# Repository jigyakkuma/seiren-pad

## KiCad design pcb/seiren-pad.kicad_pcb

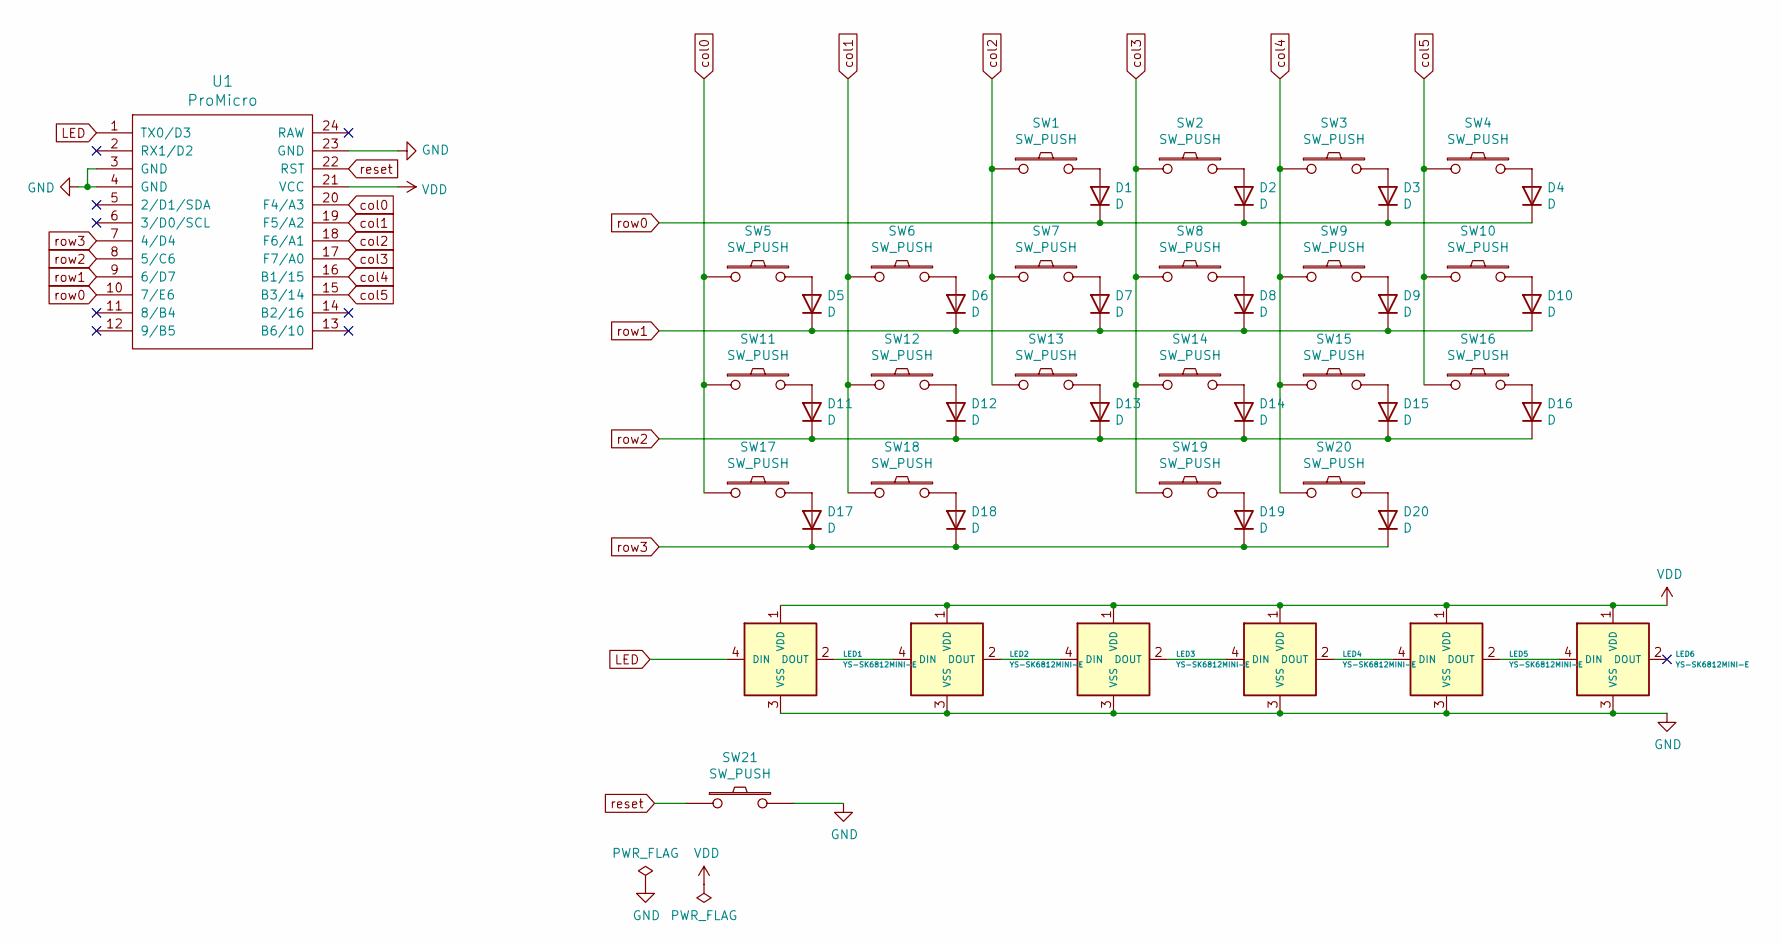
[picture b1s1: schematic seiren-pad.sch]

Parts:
D1, D2, D3, D4, D5, D6, D7, D8, D9, D10, D11, D12, D13, D14, D15, D16, D17, D18, D19, D20: D; D3_SMD_v2
LED1, LED2, LED3, LED4, LED5, LED6: YS-SK6812MINI-E
SW1, SW2, SW3, SW4, SW5, SW6, SW7, SW8, SW9, SW10, SW11, SW12, SW13, SW14, SW15, SW16, SW17, SW18, SW19, SW20: SW_PUSH; CherryMX_Hotswap
SW21: SW_PUSH; SW_Tactile_SPST_Angled_MJTP1117
U1: ProMicro; ProMicro_v3

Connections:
GND: LED1.3 (VSS), LED2.3 (VSS), LED3.3 (VSS), LED4.3 (VSS), LED5.3 (VSS), LED6.3 (VSS), SW21.2, U1.3 (GND), U1.4 (GND), U1.23 (GND)
LED: LED1.4 (DIN), U1.1 (TX0/D3)
unnamed: D1.2 (A), SW1.2
unnamed: D2.2 (A), SW2.2
unnamed: D3.2 (A), SW3.2
unnamed: D4.2 (A), SW4.2
unnamed: D5.2 (A), SW5.2
unnamed: D6.2 (A), SW6.2
unnamed: D7.2 (A), SW7.2
unnamed: D8.2 (A), SW8.2
unnamed: D9.2 (A), SW9.2
unnamed: D10.2 (A), SW10.2
unnamed: D11.2 (A), SW11.2
unnamed: D12.2 (A), SW12.2
unnamed: D13.2 (A), SW13.2
unnamed: D14.2 (A), SW14.2
unnamed: D15.2 (A), SW15.2
unnamed: D16.2 (A), SW16.2
unnamed: D17.2 (A), SW17.2
unnamed: D18.2 (A), SW18.2
unnamed: D19.2 (A), SW19.2
unnamed: D20.2 (A), SW20.2
unnamed: LED1.2 (DOUT), LED2.4 (DIN)
unnamed: LED2.2 (DOUT), LED3.4 (DIN)
unnamed: LED3.2 (DOUT), LED4.4 (DIN)
unnamed: LED4.2 (DOUT), LED5.4 (DIN)
unnamed: LED5.2 (DOUT), LED6.4 (DIN)
VDD: LED1.1 (VDD), LED2.1 (VDD), LED3.1 (VDD), LED4.1 (VDD), LED5.1 (VDD), LED6.1 (VDD), U1.21 (VCC)
col0: SW5.1, SW11.1, SW17.1, U1.20 (F4/A3)
col1: SW6.1, SW12.1, SW18.1, U1.19 (F5/A2)
col2: SW1.1, SW7.1, SW13.1, U1.18 (F6/A1)
col3: SW2.1, SW8.1, SW14.1, SW19.1, U1.17 (F7/A0)
col4: SW3.1, SW9.1, SW15.1, SW20.1, U1.16 (B1/15)
col5: SW4.1, SW10.1, SW16.1, U1.15 (B3/14)
reset: SW21.1, U1.22 (RST)
row0: D1.1 (K), D2.1 (K), D3.1 (K), D4.1 (K), U1.10 (7/E6)
row1: D5.1 (K), D6.1 (K), D7.1 (K), D8.1 (K), D9.1 (K), D10.1 (K), U1.9 (6/D7)
row2: D11.1 (K), D12.1 (K), D13.1 (K), D14.1 (K), D15.1 (K), D16.1 (K), U1.8 (5/C6)
row3: D17.1 (K), D18.1 (K), D19.1 (K), D20.1 (K), U1.7 (4/D4)

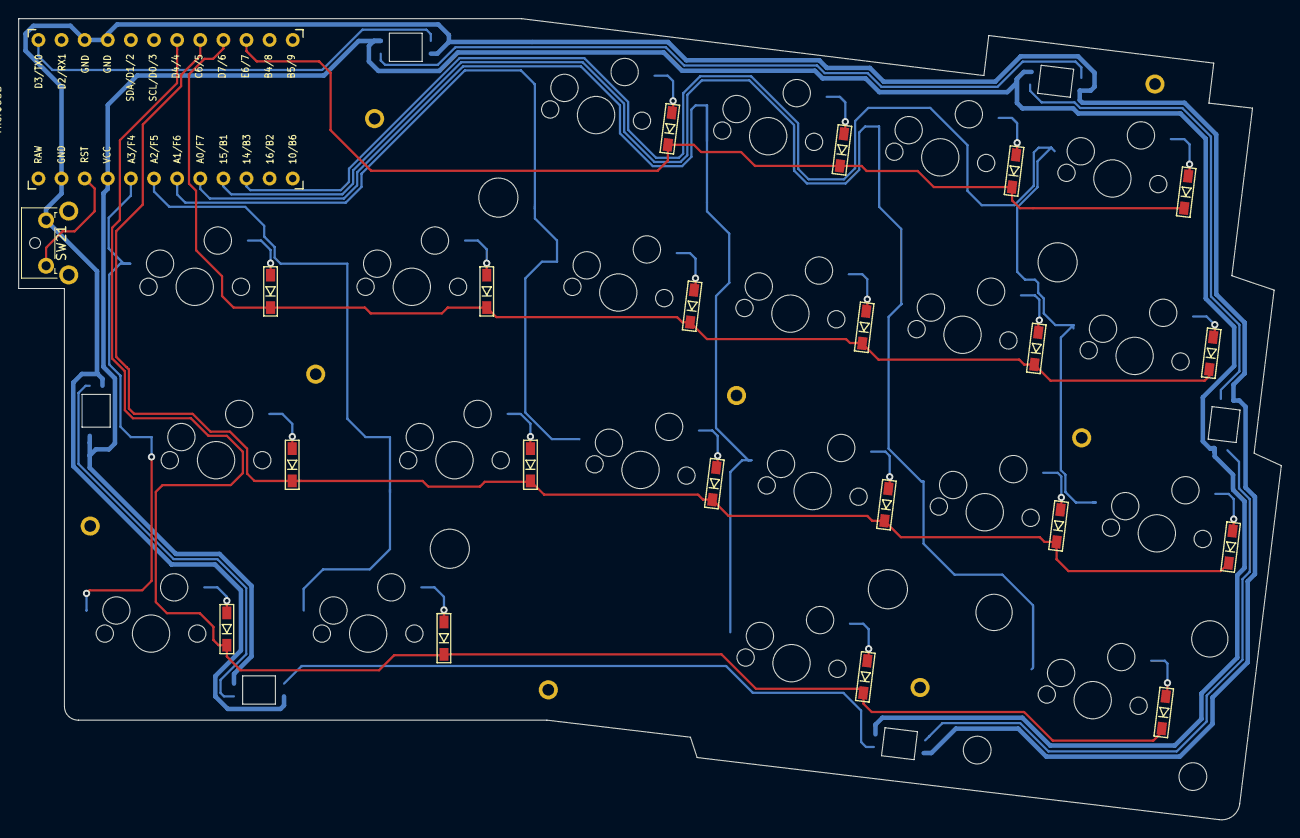
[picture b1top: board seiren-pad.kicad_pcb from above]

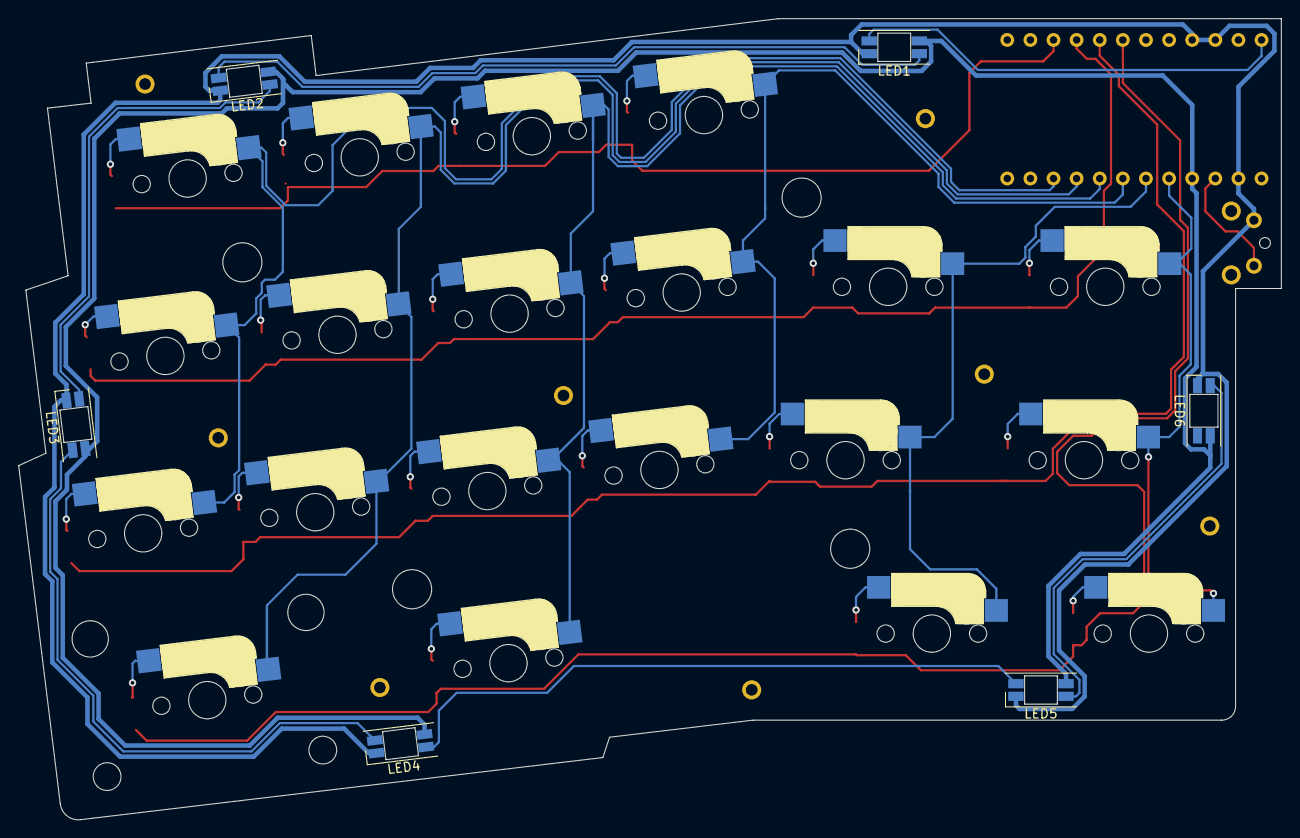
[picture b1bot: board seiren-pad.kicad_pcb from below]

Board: 2 copper layers, 138.7 x 88.0 mm, 53 parts (6 on the bottom side), 39 nets.

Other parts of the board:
Ref**: Val**; 2U_stabilizer_hole
Ref**#2, Ref**#3, Ref**#4, Ref**#5: Val**; spacer_m2
